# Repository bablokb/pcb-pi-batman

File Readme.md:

A pcb to support the battery management of mobile Pi-projects
=============================================================

Overview
--------

Since the Pi still drains power after shutdown, it is necessary
for battery-based projects to turn of the supply. This project uses
a very simple design to implement this.

One requisite is a DCDC-converter with an enable pin. As an alternative,
you can use a mosfet to switch power.

This repository contains two pcbs: the so called
_"minimal pcb"_ is nothing more than a flip-flop (SN74HC(T)74) with some
connectors for the converter and the Pi. The second pcb is a pHat designed
for a Pi-Zero.

Schematic Min-PCB
-----------------

The flip-flop drives the enable pin of the converter (pin 1Q). A button
(and/or RTC or sensor) pulls the reset pin (/1PRE) low to turn on power. A
GPIO from the Pi is connected to the clock-pin (pin 1CLK). The Pi will
pull this pin high on shutdown (see below). This will change the state
of the flip-flop: 1Q will take the value of 1D, which in turn is
connected to the inverted value /1Q (i.e. 1Q will switch to the current
value of /1Q).

The additional pin labelled _"LBO"_ is optional. Converters with a battery
monitoring can output a signal (_"low battery out"_) and if this is
connected to the Pi a program can react e.g. with an emergency
shutdown or an alarm if LBO is set.

Min-Pcb
-------

This is a very small pcb, useful if your project design needs it near
the battery pack:

The layout is simple and the complete kicad-project is available in the
directory `min-pcb`.

Schematic pHat-Pcb
------------------

This circuit is more sophisticated. The basis is the same, but it adds an
RTC (DS3231) for time-based boots and an inverter, mainly for turning on
power with a low-high transition. Also, the pcb has space for a
TPS61023 breakout (DC-DC converter) and for a KA75330 voltage-supervisor IC.

If you populate a LED+resistor, it will light up once the input
voltage drops below something like 3.15-3.45V (range of KA75330 according
to the datasheet). But in fact it might be a better idea not to
populate these two components: if voltage is low you don't want to
waste the rest of the battery for lighting up a LED?! For this reason
the inverted signal is also connected to GPIO16, so the Pi can react
and maybe shutdown or send a low-battery mail.

Another optional component is a second switch, directly attached to the Pi
(GPIO6). See the configuration section below to see how you can
shutdown the Pi with this button (you can use it for other purposes as well).

pHat-Pcb
--------

The format of the pcb is a zero-sized hat without beeing a formal pHat:

The hat breaks out most of the GPIOs, except for GPIO6, GPIO16 and GPIO26.

The following components are optional:

  - TPS61023 DC-DC converter
    (you can externaly connect battery, 5V and enable pin instead)
  - DS3131 RTC
  - KA75330 + LED + resistor
  - all connectors

Pi Configuration Min-Pcb
------------------------

The Pi has to signal shutdown to the pcb. Simply add the following
line to your `/boot/config.txt`:

    dtoverlay=gpio-poweroff,gpiopin=26

Note that the default is GPIO26 (physical pin 37). You cannot
just use any pin, since on power-on the pin has to be pulled low
until the gpio-poweroff driver takes over.

Pi Configuration pHat-Pcb
-------------------------

This pcb has multiple connections to the Pi. Add following lines to
your `/boot/config.txt`:

    dtoverlay=i2c-rtc,ds3231,wakup-source
    dtoverlay=gpio-shutdown,gpio_pin=6
    dtoverlay=gpio-poweroff,gpiopin=26
    dtoverlay=gpio-key,gpio=16,active_low=0,gpio_pull=off,label=lbo,keycode=xx

The first line is to activate the rtc, the last line triggers the
configured key on a battery low signal. This is just an example, there
are other ways to monitor GPIO16 for a low-high transition.

For the rtc you need an additional file `/etc/udev/rules.d/85-hwclock.rules`
with the content:

    KERNEL=="rtc0", RUN+="/sbin/hwclock -s -u -f $root/$name"

License
-------

Shield: [![CC BY-SA 4.0][cc-by-sa-shield]][cc-by-sa]

This work is licensed under a
[Creative Commons Attribution-ShareAlike 4.0 International
License][cc-by-sa].

[![CC BY-SA 4.0][cc-by-sa-image]][cc-by-sa]

[cc-by-sa]: http://creativecommons.org/licenses/by-sa/4.0/
[cc-by-sa-image]: https://licensebuttons.net/l/by-sa/4.0/88x31.png
[cc-by-sa-shield]:
https://img.shields.io/badge/License-CC%20BY--SA%204.0-lightgrey.svg

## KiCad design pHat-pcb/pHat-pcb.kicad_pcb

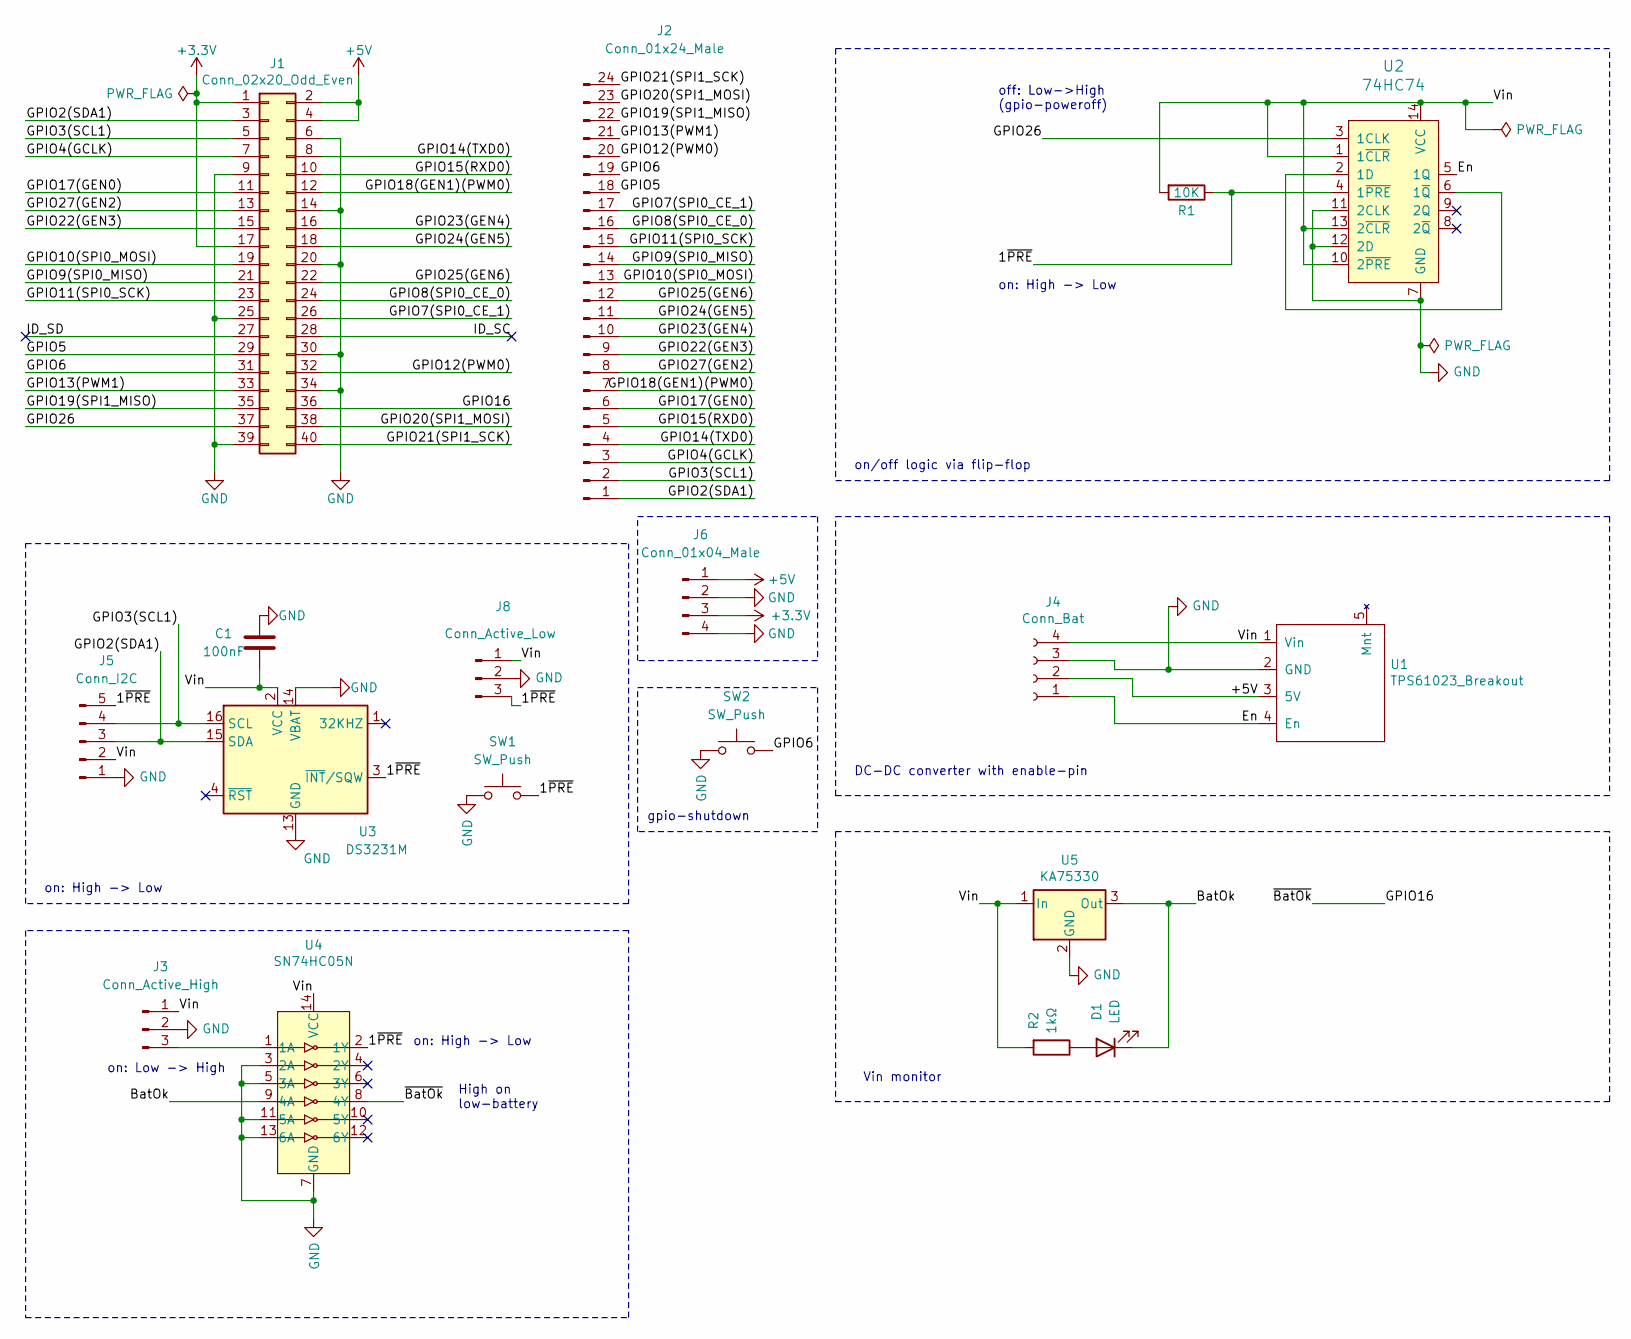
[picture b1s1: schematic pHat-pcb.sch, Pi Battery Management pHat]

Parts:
C1: 100nF; C_1206_3216Metric_Pad1.33x1.80mm_HandSolder
D1: LED; LED_1206_3216Metric_Pad1.42x1.75mm_HandSolder
J1: Conn_02x20_Odd_Even; PinSocket_2x20_P2.54mm_Vertical
J2: Conn_01x24_Male; PinHeader_1x24_P2.54mm_Vertical
J3: Conn_Active_High; PinHeader_1x03_P2.54mm_Vertical
J4: Conn_Bat; TerminalBlock_TE_282834-4_1x04_P2.54mm_Horizontal
J5: Conn_I2C; PinHeader_1x05_P2.54mm_Vertical
J6: Conn_01x04_Male; PinHeader_1x04_P2.54mm_Vertical
J8: Conn_Active_Low; PinHeader_1x03_P2.54mm_Vertical
R1: 10K; R_1206_3216Metric_Pad1.30x1.75mm_HandSolder
R2: 1kΩ; R_1206_3216Metric_Pad1.30x1.75mm_HandSolder
SW1, SW2: SW_Push; SW_PUSH_SLIM_1x4
U1: TPS61023_Breakout
U2: 74HC74; SO-14_3.9x8.65mm_P1.27mm_HandSolder; MPN SN74HC74N; Digi-Key_PN 296-1602-5-ND
U3: DS3231M; SOIC-16W_7.5x10.3mm_P1.27mm_HandSolder
U4: SN74HC05N; SO-14_3.9x8.65mm_P1.27mm_HandSolder
U5: KA75330; TO-92_Inline_Wide

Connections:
+3V3: J1.1, J1.17, J6.3
+5V: J1.2, J1.4, J4.2, J6.1, U1.3 (5V)
/1~PRE: J5.5, J8.3, R1.1, SW1.2, U2.4 (1~PRE), U3.3 (~INT~/SQW), U4.2 (1Y)
/BatOk: D1.1 (K), U4.9 (4A), U5.3 (Out)
/En: J4.1, U1.4 (En), U2.5 (1Q)
/GPIO2(SDA1): J1.3, J2.1, J5.3, U3.15 (SDA)
/GPIO3(SCL1): J1.5, J2.2, J5.4, U3.16 (SCL)
/GPIO4(GCLK): J1.7, J2.3
/GPIO5: J1.29, J2.18
/GPIO6: J1.31, J2.19, SW2.2
/GPIO7(SPI0_CE_1): J1.26, J2.17
/GPIO8(SPI0_CE_0): J1.24, J2.16
/GPIO9(SPI0_MISO): J1.21, J2.14
/GPIO10(SPI0_MOSI): J1.19, J2.13
/GPIO11(SPI0_SCK): J1.23, J2.15
/GPIO12(PWM0): J1.32, J2.20
/GPIO13(PWM1): J1.33, J2.21
/GPIO14(TXD0): J1.8, J2.4
/GPIO15(RXD0): J1.10, J2.5
/GPIO16: J1.36, U4.8 (4Y)
/GPIO17(GEN0): J1.11, J2.6
/GPIO18(GEN1)(PWM0): J1.12, J2.7
/GPIO19(SPI1_MISO): J1.35, J2.22
/GPIO20(SPI1_MOSI): J1.38, J2.23
/GPIO21(SPI1_SCK): J1.40, J2.24
/GPIO22(GEN3): J1.15, J2.9
/GPIO23(GEN4): J1.16, J2.10
/GPIO24(GEN5): J1.18, J2.11
/GPIO25(GEN6): J1.22, J2.12
/GPIO26: J1.37, U2.3 (1CLK)
/GPIO27(GEN2): J1.13, J2.8
/ID_SC: J1.28
/ID_SD: J1.27
/Vin: C1.2, J3.1, J4.4, J5.2, J8.1, R1.2, R2.2, U1.1 (Vin), U2.1 (1~CLR), U2.10 (2~PRE), U2.13 (2~CLR), U2.14 (VCC), U3.2 (VCC), U4.14 (VCC), U5.1 (In)
GND: C1.1, J1.6, J1.9, J1.14, J1.20, J1.25, J1.30, J1.34, J1.39, J3.2, J4.3, J5.1, J6.2, J6.4, J8.2, SW1.1, SW2.1, U1.2 (GND), U2.7 (GND), U2.11 (2CLK), U2.12 (2D), U3.5 (GND), U3.6 (GND), U3.7 (GND), U3.8 (GND), U3.9 (GND), U3.10 (GND), U3.11 (GND), U3.12 (GND), U3.13 (GND), U3.14 (VBAT), U4.3 (2A), U4.5 (3A), U4.7 (GND), U4.11 (5A), U4.13 (6A), U5.2 (GND)
unnamed: D1.2 (A), R2.1
unnamed: J3.3, U4.1 (1A)
unnamed: U2.2 (1D), U2.6 (1~Q)

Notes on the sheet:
off: Low->High (gpio-poweroff)
on: High -> Low
on: Low -> High
on/off logic via flip-flop
DC-DC converter with enable-pin
High on low-battery
Vin monitor
gpio-shutdown

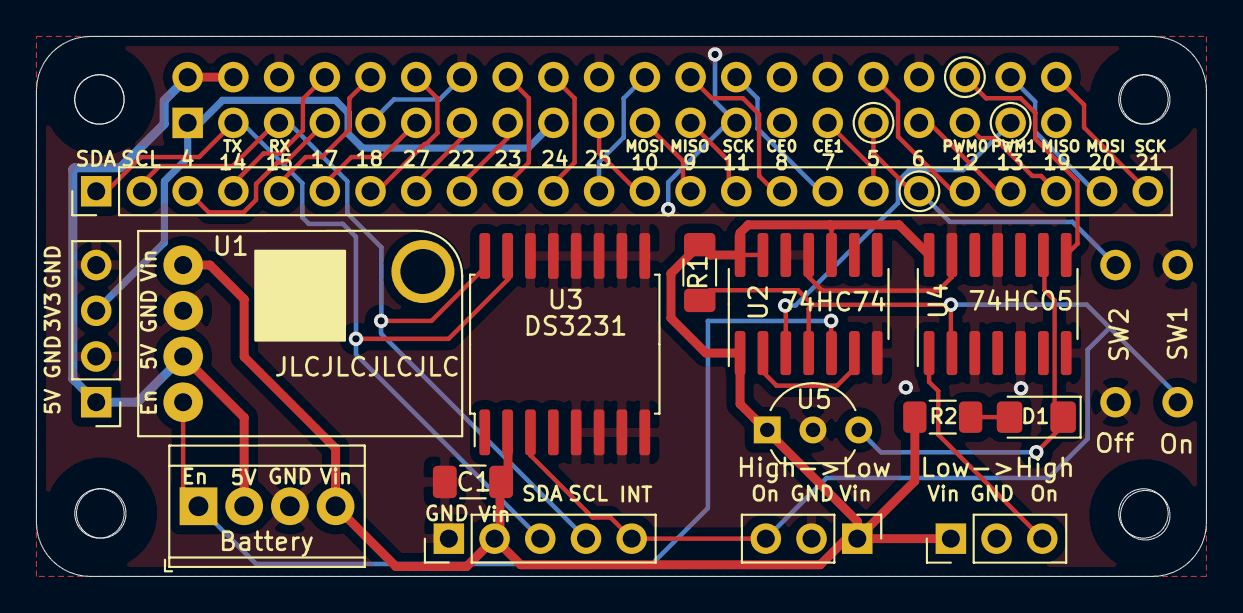
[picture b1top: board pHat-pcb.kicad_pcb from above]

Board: 2 copper layers, 65.0 x 30.0 mm, 18 parts (1 on the bottom side), 36 nets.

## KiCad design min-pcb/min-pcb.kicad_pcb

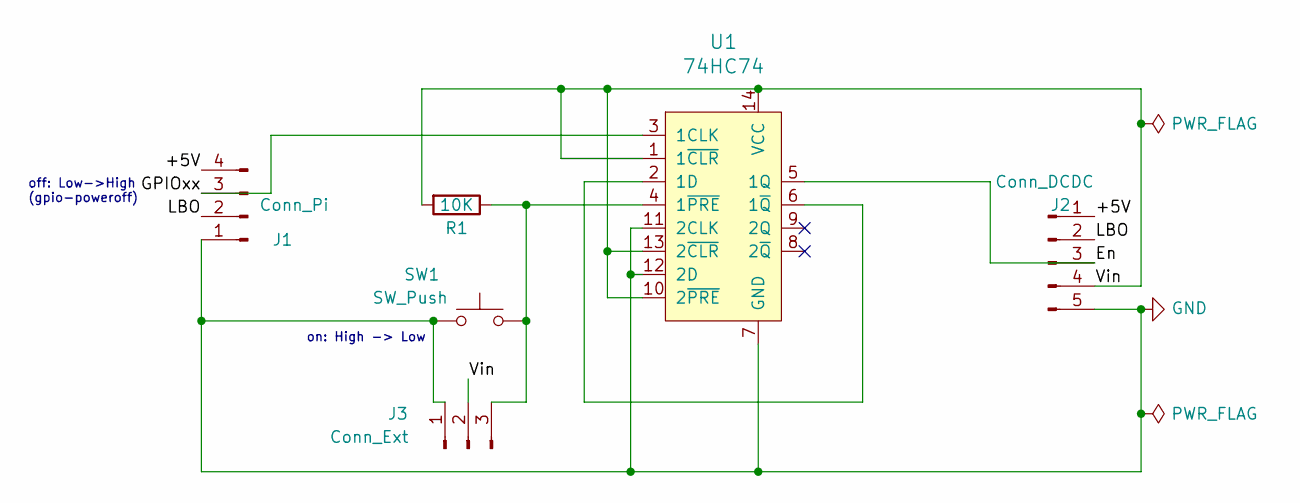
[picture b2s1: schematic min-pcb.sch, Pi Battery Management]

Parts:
J1: Conn_Pi; PinHeader_1x04_P2.54mm_Horizontal
J2: Conn_DCDC; PinHeader_1x05_P2.54mm_Horizontal
J3: Conn_Ext; PinHeader_1x03_P2.54mm_Horizontal
R1: 10K; R_Axial_DIN0207_L6.3mm_D2.5mm_P7.62mm_Horizontal
SW1: SW_Push; SW_PUSH_6mm_H9.5mm
U1: 74HC74; DIP-14_W7.62mm_Socket; MPN SN74HC74N; Digi-Key_PN 296-1602-5-ND

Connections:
/+5V: J1.4, J2.1
/En: J2.3, U1.5 (1Q)
/GPIOxx: J1.3, U1.3 (1CLK)
/LBO: J1.2, J2.2
/Vin: J2.4, J3.2, R1.2, U1.1 (1~CLR), U1.10 (2~PRE), U1.13 (2~CLR), U1.14 (VCC)
GND: J1.1, J2.5, J3.1, SW1.1, U1.7 (GND), U1.11 (2CLK), U1.12 (2D)
unnamed: J3.3, R1.1, SW1.2, U1.4 (1~PRE)
unnamed: U1.2 (1D), U1.6 (1~Q)

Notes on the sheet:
off: Low->High (gpio-poweroff)
on: High -> Low

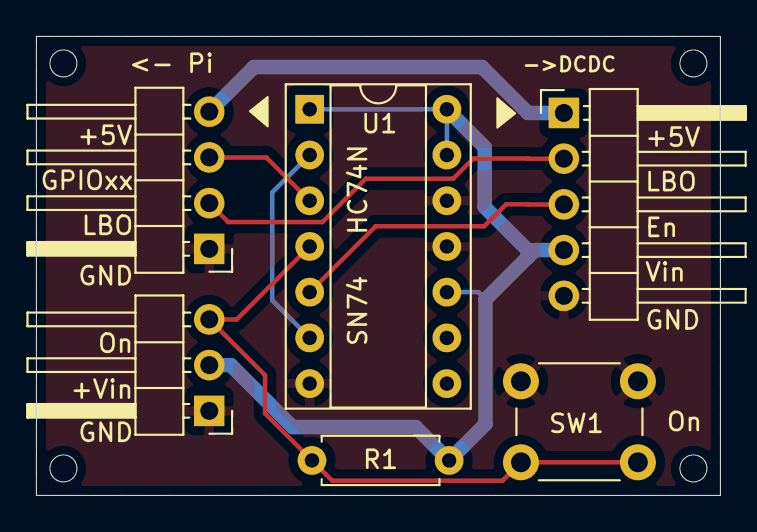
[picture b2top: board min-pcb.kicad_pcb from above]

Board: 2 copper layers, 38.0 x 25.5 mm, 6 parts (0 on the bottom side), 8 nets.

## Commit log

2020-09-22 Rev1
2020-09-22 optimzed traces
2020-09-22 rearranged pins on connectors
2020-09-23 Rev2: added power to external connector, added mounting-holes
2020-09-23 plot-options for gerber-export
2020-09-24 minor adjustment of connector positions to have some space for terminal-blocks
2020-09-26 added textfield for JLC production-number
2020-10-06 Rev 1: layout complete
2020-10-07 bugfix: labels +5V/GPIOxx were swapped on J1 (Pi-connector)
2020-10-07 additional labels on the bottom
2020-10-07 updated images after label-fix
2020-10-09 minor text changes
2020-10-12 replaced 74HCT74 with 74HC74
2020-10-12 bugfix: replace 74HCT74 with 74HC74
2020-10-17 added capacitor to DS3231
2020-10-17 recreate rescue lib
2020-10-17 removed external LBO connector
2020-10-17 Rev2: with DS3231 cap and no LBO-connector
2020-10-21 Rev3: added power-control IC and LED
2020-10-21 Rev4: added interrupt-pin for external I2C-connector
2020-10-23 replaced 74HC03 (nand) with 74HC05 (inverter)
2020-10-23 Rev5: drive LED from GPIO06
2020-10-27 Rev6: add connector for 5V, 3V3 and GND
2020-10-28 Rev7: added shutdown-button
2020-10-30 Rev8: add 5V to external battery connector / fixed KA75330 pin-order / updated labels
2020-12-15 added section for pHat
2020-12-15 bugfix: prevent 2nd flip-flop from floating
2020-12-21 link to image of pHat
2021-10-30 changed LICENSE to CC-BY-SA
2021-10-30 added section about license
